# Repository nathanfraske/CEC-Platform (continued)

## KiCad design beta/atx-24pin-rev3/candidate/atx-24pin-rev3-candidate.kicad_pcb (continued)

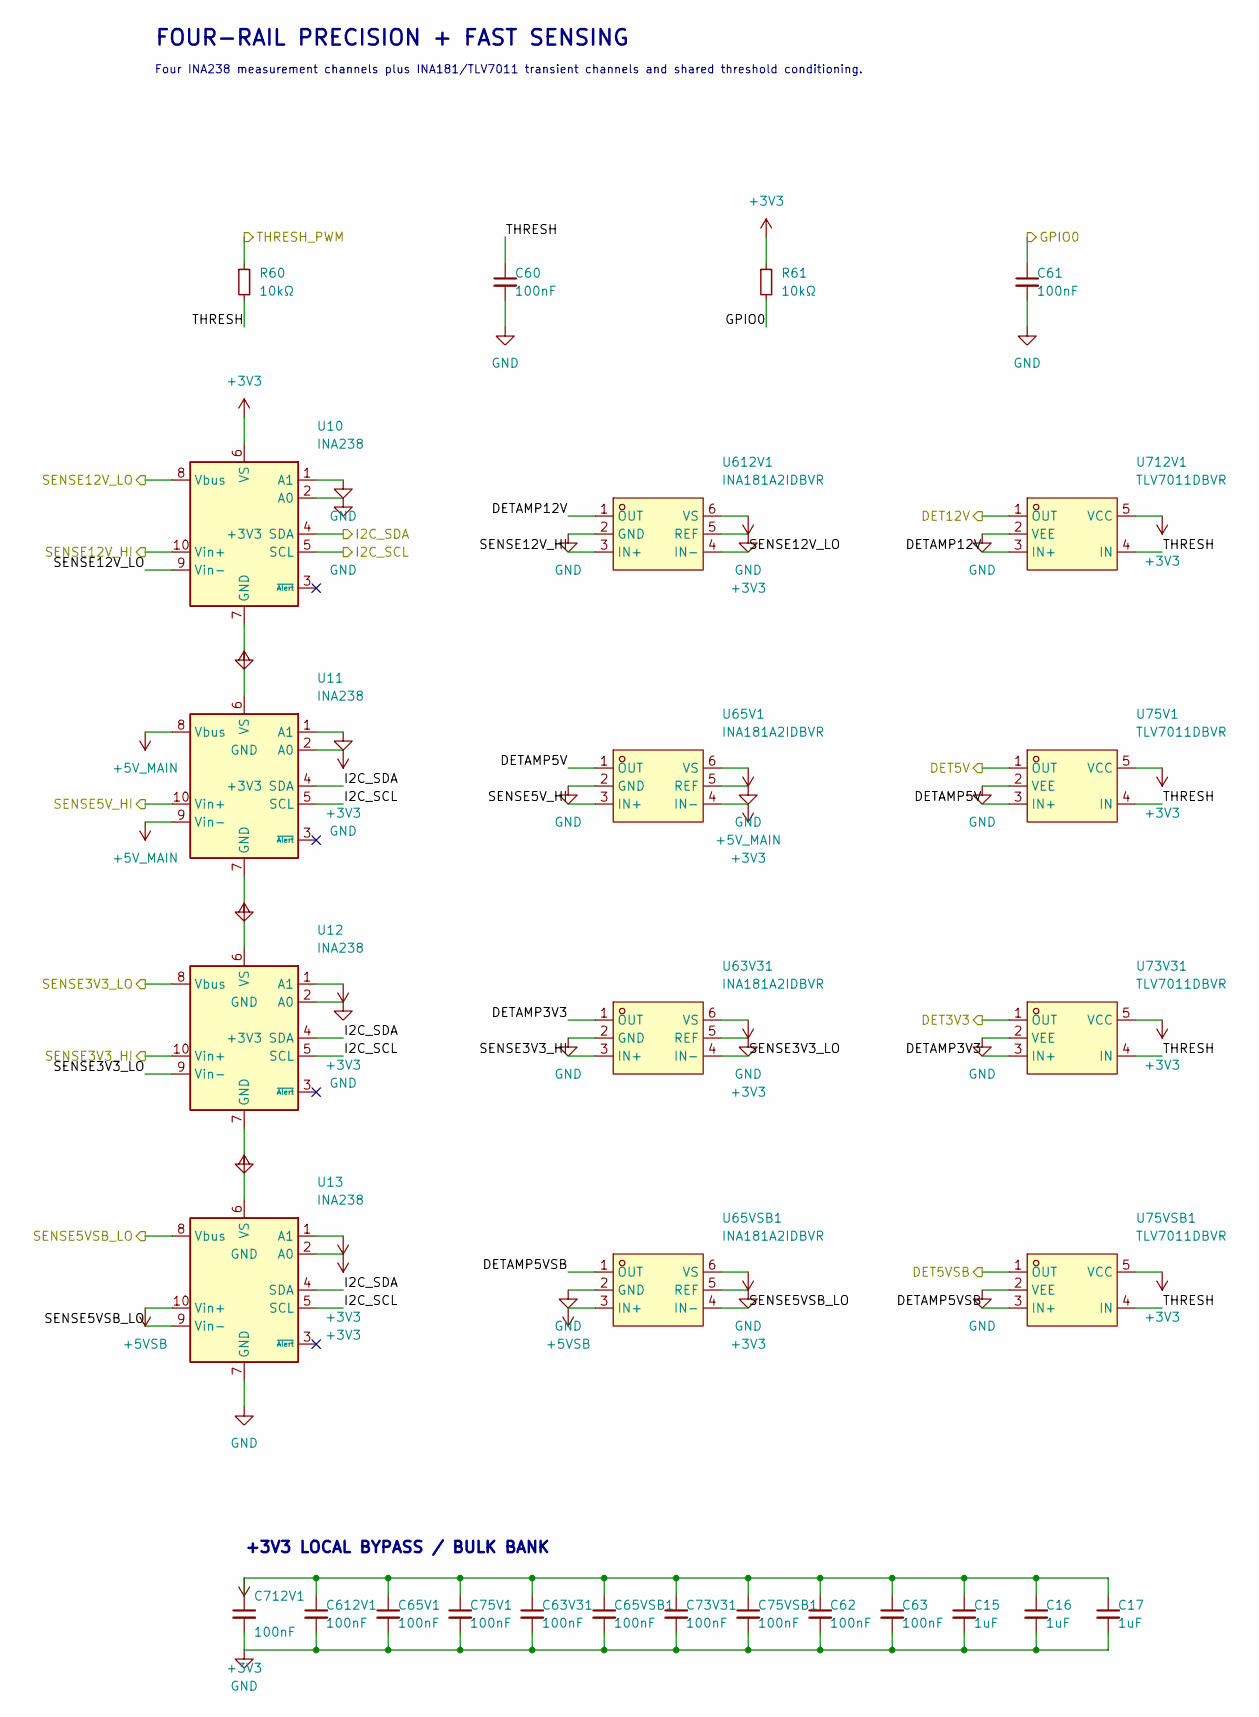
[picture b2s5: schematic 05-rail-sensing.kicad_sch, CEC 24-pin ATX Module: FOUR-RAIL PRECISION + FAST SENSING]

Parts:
C15, C16, C17: 1uF; C_0603_1608Metric; MPN CL10B105KA8NNNC; LCSC C29936
C60, C61, C62, C63, C63V31, C65V1, C65VSB1, C73V31, C75V1, C75VSB1, C612V1, C712V1: 100nF; C_0402_1005Metric; MPN CL05B104KO5NNNC; LCSC C1525
R60, R61: 10kΩ; R_0402_1005Metric; MPN 0402WGF1002TCE; LCSC C25744
U10, U11, U12, U13: INA238; VSSOP-10_3x3mm_P0.5mm; MPN INA238AIDGSR; LCSC C2868250
U63V31, U65V1, U65VSB1, U612V1: INA181A2IDBVR; SOT-23-6; MPN INA181A2IDBVR; LCSC C2058784
U73V31, U75V1, U75VSB1, U712V1: TLV7011DBVR; SOT-23-5; MPN TLV7011DBVR; LCSC C702117

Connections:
+3V3: C15.1, C16.1, C17.1, C62.1, C63.1, C63V31.1, C65V1.1, C65VSB1.1, C73V31.1, C75V1.1, C75VSB1.1, C612V1.1, C712V1.1, R61.1, U10.6 (VS), U11.2 (A0), U11.6 (VS), U12.1 (A1), U12.6 (VS), U13.1 (A1), U13.2 (A0), U13.6 (VS), U63V31.6 (VS), U65V1.6 (VS), U65VSB1.6 (VS), U73V31.5 (VCC), U75V1.5 (VCC), U75VSB1.5 (VCC), U612V1.6 (VS), U712V1.5 (VCC); also elsewhere on the board
+5VSB: U13.10 (Vin+), U65VSB1.3 (IN+); also elsewhere on the board
+5V_MAIN: U11.8 (Vbus), U11.9 (Vin-), U65V1.4 (IN-); also elsewhere on the board
/DET3V3: U73V31.1 (OUT); also elsewhere on the board
/DET5V: U75V1.1 (OUT); also elsewhere on the board
/DET5VSB: U75VSB1.1 (OUT); also elsewhere on the board
/DET12V: U712V1.1 (OUT); also elsewhere on the board
/FOUR-RAIL PRECISION + FAST SENSING/DETAMP3V3: U63V31.1 (OUT), U73V31.3 (IN+)
/FOUR-RAIL PRECISION + FAST SENSING/DETAMP5V: U65V1.1 (OUT), U75V1.3 (IN+)
/FOUR-RAIL PRECISION + FAST SENSING/DETAMP5VSB: U65VSB1.1 (OUT), U75VSB1.3 (IN+)
/FOUR-RAIL PRECISION + FAST SENSING/DETAMP12V: U612V1.1 (OUT), U712V1.3 (IN+)
/FOUR-RAIL PRECISION + FAST SENSING/THRESH: C60.1, R60.2, U73V31.4 (IN), U75V1.4 (IN), U75VSB1.4 (IN), U712V1.4 (IN)
/GPIO0: C61.1, R61.2; also elsewhere on the board
/I2C_SCL: U10.5 (SCL), U11.5 (SCL), U12.5 (SCL), U13.5 (SCL); also elsewhere on the board
/I2C_SDA: U10.4 (SDA), U11.4 (SDA), U12.4 (SDA), U13.4 (SDA); also elsewhere on the board
/SENSE3V3_HI: U12.10 (Vin+), U63V31.3 (IN+); also elsewhere on the board
/SENSE3V3_LO: U12.8 (Vbus), U12.9 (Vin-), U63V31.4 (IN-); also elsewhere on the board
/SENSE5VSB_LO: U13.8 (Vbus), U13.9 (Vin-), U65VSB1.4 (IN-); also elsewhere on the board
/SENSE5V_HI: U11.10 (Vin+), U65V1.3 (IN+); also elsewhere on the board
/SENSE12V_HI: U10.10 (Vin+), U612V1.3 (IN+); also elsewhere on the board
/SENSE12V_LO: U10.8 (Vbus), U10.9 (Vin-), U612V1.4 (IN-); also elsewhere on the board
/THRESH_PWM: R60.1; also elsewhere on the board
GND: C15.2, C16.2, C17.2, C60.2, C61.2, C62.2, C63.2, C63V31.2, C65V1.2, C65VSB1.2, C73V31.2, C75V1.2, C75VSB1.2, C612V1.2, C712V1.2, U10.1 (A1), U10.2 (A0), U10.7 (GND), U11.1 (A1), U11.7 (GND), U12.2 (A0), U12.7 (GND), U13.7 (GND), U63V31.2 (GND), U63V31.5 (REF), U65V1.2 (GND), U65V1.5 (REF), U65VSB1.2 (GND), U65VSB1.5 (REF), U73V31.2 (VEE), U75V1.2 (VEE), U75VSB1.2 (VEE), U612V1.2 (GND), U612V1.5 (REF), U712V1.2 (VEE); also elsewhere on the board

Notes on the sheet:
FOUR-RAIL PRECISION + FAST SENSING
Four INA238 measurement channels plus INA181/TLV7011 transient channels and shared threshold conditioning.
+3V3 LOCAL BYPASS / BULK BANK

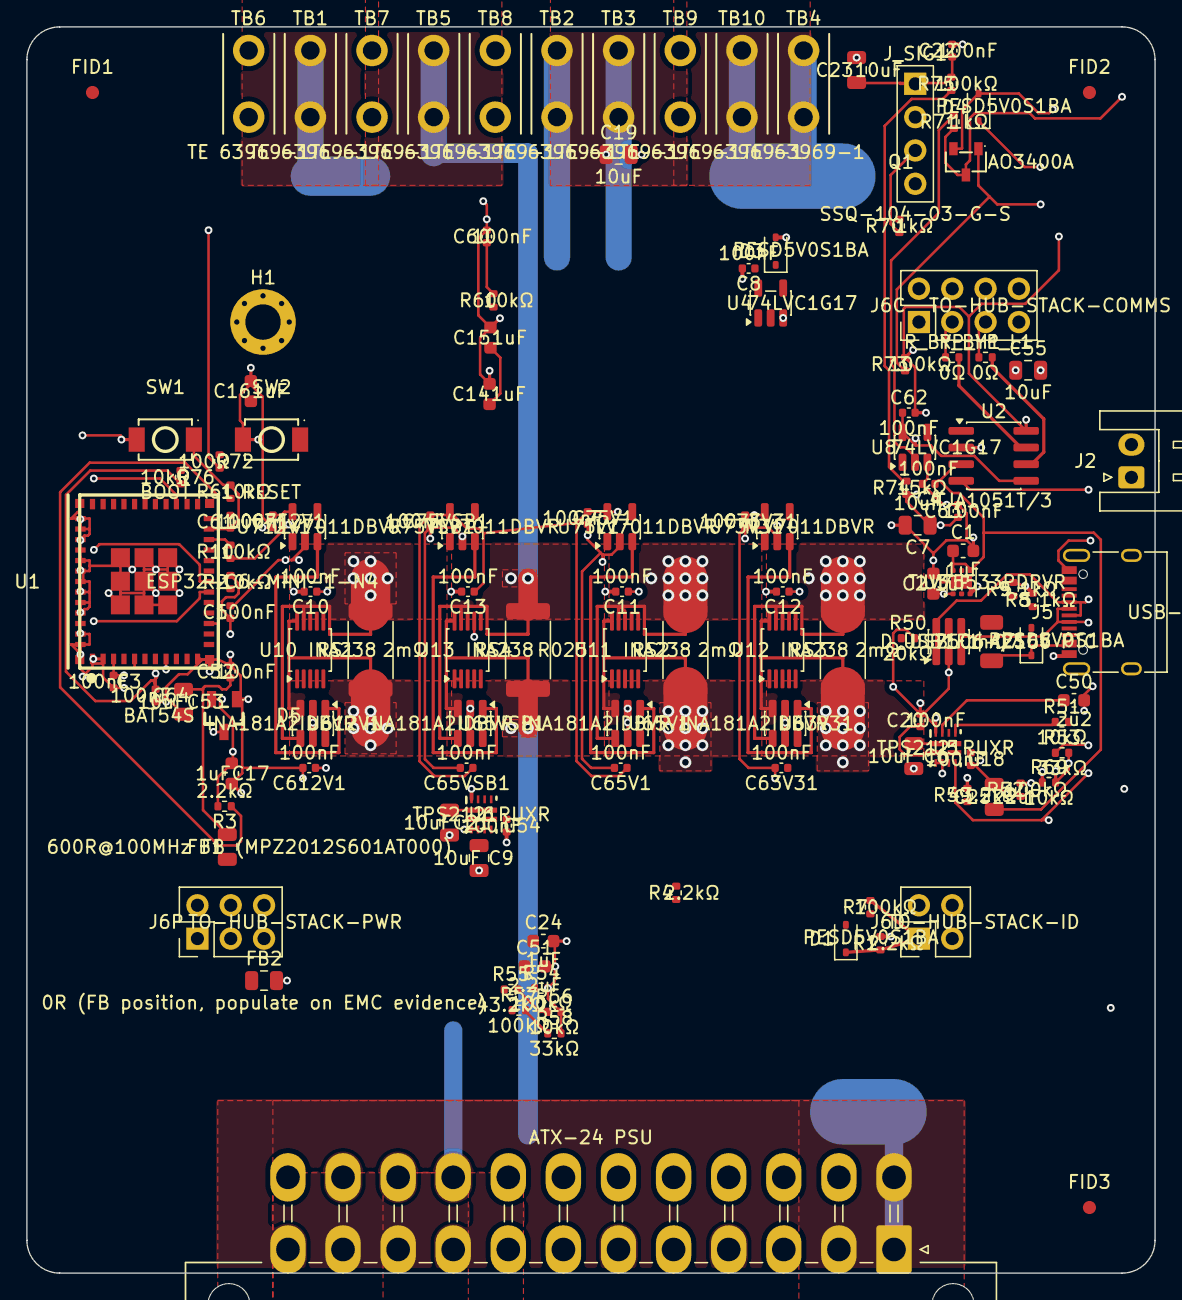
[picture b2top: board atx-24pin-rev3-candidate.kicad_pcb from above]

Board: 6 copper layers, 86.0 x 95.0 mm, 130 parts (0 on the bottom side), 63 nets.

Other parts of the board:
FID1, FID2, FID3: Fiducial_1mm_Mask2mm
H1: MountingHole_2.7mm_M2.5_Pad_Via

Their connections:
GND: H1.1; also elsewhere on the board

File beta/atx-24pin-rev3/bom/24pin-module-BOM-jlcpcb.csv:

"Comment","Designator","Footprint","LCSC Part #"
"1uF","C1,C2,C14,C15,C16,C17,C24","cec-Capacitor_SMD:C_0603_1608Metric","C29936"
"22uF","C25","cec-Capacitor_SMD:C_0805_2012Metric","C45783"
"100nF","C3,C4,C5,C8,C10,C11,C12,C13,C18,C20,C22,C52,C54,C60,C61,C62,C63,C63V31,C64,C65V1,C65VSB1,C73V31,C75V1,C75VSB1,C612V1,C712V1","cec-Capacitor_SMD:C_0402_1005Metric","C1525"
"2u2","C50","cec-Capacitor_SMD:C_0603_1608Metric","C23630"
"2.2uF","C51","cec-Capacitor_SMD:C_0603_1608Metric","C23630"
"10uF","C6,C7,C9,C19,C21,C23,C53,C55","cec-Capacitor_SMD:C_0805_2012Metric","C15850"
"PESD5V0S1BA","D1,D3,D4,D7","cec-Diode_SMD:D_SOD-323","C5261083"
"BAT54S","D5","cec-Package_TO_SOT_SMD:SOT-23-3_L2.9-W1.3-P1.90-LS2.4-TL","C545549"
"USBLC6-2SC6","D_USB1","cec-Package_TO_SOT_SMD:SOT-23-6","C7519"
"750mA/16V PTC","F1","cec-Resistor_SMD:R_1206_3216Metric","C371166"
"600R@100MHz FB (MPZ2012S601AT000)","FB1","cec-Capacitor_SMD:C_0805_2012Metric","C21519"
"0R (FB position, populate on EMC evidence)","FB2","cec-Capacitor_SMD:C_0805_2012Metric","C17477"
"TO-HUB-PWR","J2","cec-Connector_JST:JST_XH_S2B-XH-A_1x02_P2.50mm_Horizontal","C157931"
"ATX-24 PSU","J3","cec-Connector_Molex:Molex_Mini-Fit_Jr_5569-24A1_2x12_P4.20mm_Horizontal",""
"USB-C 2.0","J5","cec-Connector_USB:USB_C_Receptacle_XKB_U262-16XN-4BVC11","C319148"
"TO-HUB-STACK-COMMS","J6C?","cec-Connector_PinHeader_2.54mm:PinHeader_2x04_P2.54mm_Vertical",""
"TO-HUB-STACK-ID","J6D?","cec-Connector_PinHeader_2.54mm:PinHeader_2x02_P2.54mm_Vertical",""
"TO-HUB-STACK-PWR","J6P?","cec-Connector_PinHeader_2.54mm:PinHeader_2x03_P2.54mm_Vertical",""
"SSQ-104-03-G-S","J_SIG1","cec-Connector_PinSocket_2.54mm:PinSocket_1x04_P2.54mm_Vertical",""
"AO3400A","Q1","cec-Package_TO_SOT_SMD:SOT-23-3_L2.9-W1.3-P1.90-LS2.4-BR","C20917"
"2.2kΩ","R1,R3,R4","cec-Resistor_SMD:R_0402_1005Metric","C25879"
"10kΩ","R2,R10,R51,R56,R60,R61,R69,R76","cec-Resistor_SMD:R_0402_1005Metric","C25744"
"20kΩ","R50","cec-Resistor_SMD:R_0402_1005Metric","C25765"
"33kΩ","R53,R58","cec-Resistor_SMD:R_0402_1005Metric","C25779"
"43.2kΩ","R55,R59","cec-Resistor_SMD:R_0402_1005Metric","C25894"
"100kΩ","R7,R52,R54,R57,R73,R75","cec-Resistor_SMD:R_0402_1005Metric","C25741"
"1kΩ","R70,R71","cec-Resistor_SMD:R_0402_1005Metric","C11702"
"100Ω","R72","cec-Resistor_SMD:R_0402_1005Metric","C106233"
"15kΩ","R74","cec-Resistor_SMD:R_0402_1005Metric","C25756"
"5.1kΩ","R8,R9","cec-Resistor_SMD:R_0402_1005Metric","C25905"
"2mΩ","RS1,RS2,RS3","cec-Resistor_SMD:R_2512_6332Metric","C1729157"
"R025","RS4","cec-Resistor_SMD:R_2512_6332Metric","C494568"
"0Ω","R_BYP_H1,R_BYP_L1","cec-Resistor_SMD:R_0402_1005Metric","C17168"
"BOOT","SW1","cec-Button_Switch_SMD:TS-1088-AR02016","C720477"
"RESET","SW2","cec-Button_Switch_SMD:TS-1088-AR02016","C720477"
"TE 63969-1","TB1,TB2,TB3,TB4,TB5,TB6,TB7,TB8,TB9,TB10","cec-Connector_Blade:TE_63969_FASTON_Receptacle_250_Vertical_THT","C2961150"
"ESP32-C6-MINI-1-N4","U1","cec-RF_Module:ESP32-C6-MINI-1","C5736265"
"INA238","U10,U11,U12,U13","cec-Package_SO:VSSOP-10_3x3mm_P0.5mm","C2868250"
"TJA1051T/3","U2","cec-Package_SO:SOIC-8_3.9x4.9mm_P1.27mm","C38695"
"TLV75533PDRVR","U3","cec-Package_SON:WSON-6-1EP_2x2mm_P0.65mm_EP1x1.6mm","C2861750"
"74LVC1G17","U4,U8","cec-Package_TO_SOT_SMD:SOT-23-5","C7836"
"TPS2121RUXR","U5,U6","cec-Package_DFN_QFN:RUX0012A","C485916"
"INA181A2IDBVR","U63V31,U65V1,U65VSB1,U612V1","cec-Package_TO_SOT_SMD:SOT-23-6","C2058784"
"TLV7011DBVR","U73V31,U75V1,U75VSB1,U712V1","cec-Package_TO_SOT_SMD:SOT-23-5","C702117"

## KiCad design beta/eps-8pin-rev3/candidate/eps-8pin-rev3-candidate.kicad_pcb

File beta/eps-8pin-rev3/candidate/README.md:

# `candidate/`: the current best routed board for this module

ONE board file, kept current by the wave (owner directive 2026-07-25: "the current
best should be placed into a candidate folder per board and kept current with only
one board ideally so we have a reference").

`<board>-candidate.kicad_pcb` (+ its `.kicad_pro` / `.kicad_dru` sidecars) is a COPY
of the best board the wave has ever published for this module, with `candidate.json`
recording where it came from and how it graded. Open it to see the real current
state of the layout without digging through `build/fresh-wave-*/`.

RULES the wave enforces on every publish:
  * SCHEMATIC FRESHNESS outranks score: a winner matching more of the CURRENT
    component signatures replaces the reference even on a worse score, and a
    staler board never replaces a fresher one. The signature covers value,
    footprint, and numbered-pad nets. `schematic_match` and `schematic_exact` in
    `candidate.json` record the result. A board that grades well but predates a
    schematic or footprint change is the worse reference;
  * otherwise it replaces this file only when the new winner BEATS the recorded
    `sort_key` (lower is better -- the same ranking the wave itself uses);
  * a routed winner always beats a placement-only one, and a placement-only winner
    NEVER overwrites a routed reference;
  * exactly one `.kicad_pcb` lives here -- stale board files are pruned.

`candidate.json` is also refreshable without publishing a board. Consumers that
use a candidate as a placement oracle or materialization template MUST require
`schematic_exact: true` after a current refresh. A stale candidate remains useful
for historical outline, connector, mount, and copper review, but it is not a
component-inventory or pin/net authority.

This is a REFERENCE, not the board of record: it is machine-written, so never hand-edit
it (edits are silently overwritten by the next better wave). The authoritative
schematic + the module's own project files stay in the parent directory.

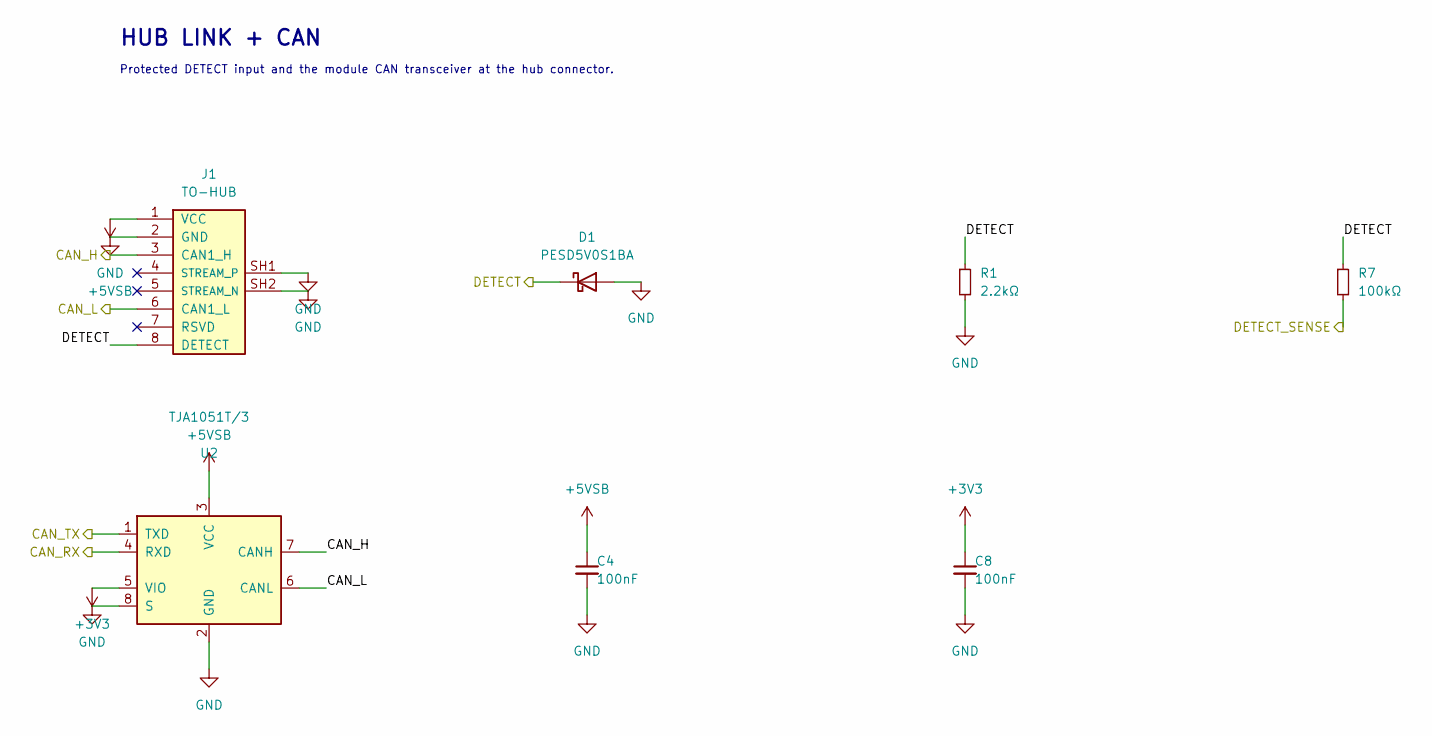
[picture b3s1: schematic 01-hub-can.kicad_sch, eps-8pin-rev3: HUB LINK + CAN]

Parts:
C4, C8: 100nF; C_0402_1005Metric; MPN CL05B104KO5NNNC; LCSC C1525
D1: PESD5V0S1BA; D_SOD-323; MPN PESD5V0S1BA; LCSC C5261083
J1: TO-HUB; RJ45_FTP_Shielded_Horizontal; MPN KH-RJ45-58-8P8C; LCSC C2683360
R1: 2.2kΩ; R_0402_1005Metric; MPN 0402WGF2201TCE; LCSC C25879
R7: 100kΩ; R_0402_1005Metric; MPN 0402WGF1003TCE; LCSC C25741
U2: TJA1051T/3; SOIC-8_3.9x4.9mm_P1.27mm; MPN TJA1051T/3/1J; LCSC C38695

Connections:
+3V3: C8.1, U2.5 (VIO); also elsewhere on the board
+5VSB: C4.1, J1.1 (VCC), U2.3 (VCC); also elsewhere on the board
/CAN_H: J1.3 (CAN1_H), U2.7 (CANH)
/CAN_L: J1.6 (CAN1_L), U2.6 (CANL)
/CAN_RX: U2.4 (RXD); also elsewhere on the board
/CAN_TX: U2.1 (TXD); also elsewhere on the board
/DETECT: D1.1 (K), J1.8 (DETECT), R1.1, R7.1
/DETECT_SENSE: R7.2; also elsewhere on the board
GND: C4.2, C8.2, D1.2 (A), J1.2 (GND), J1.SH1, J1.SH2, R1.2, U2.2 (GND), U2.8 (S); also elsewhere on the board

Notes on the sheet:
HUB LINK + CAN
Protected DETECT input and the module CAN transceiver at the hub connector.

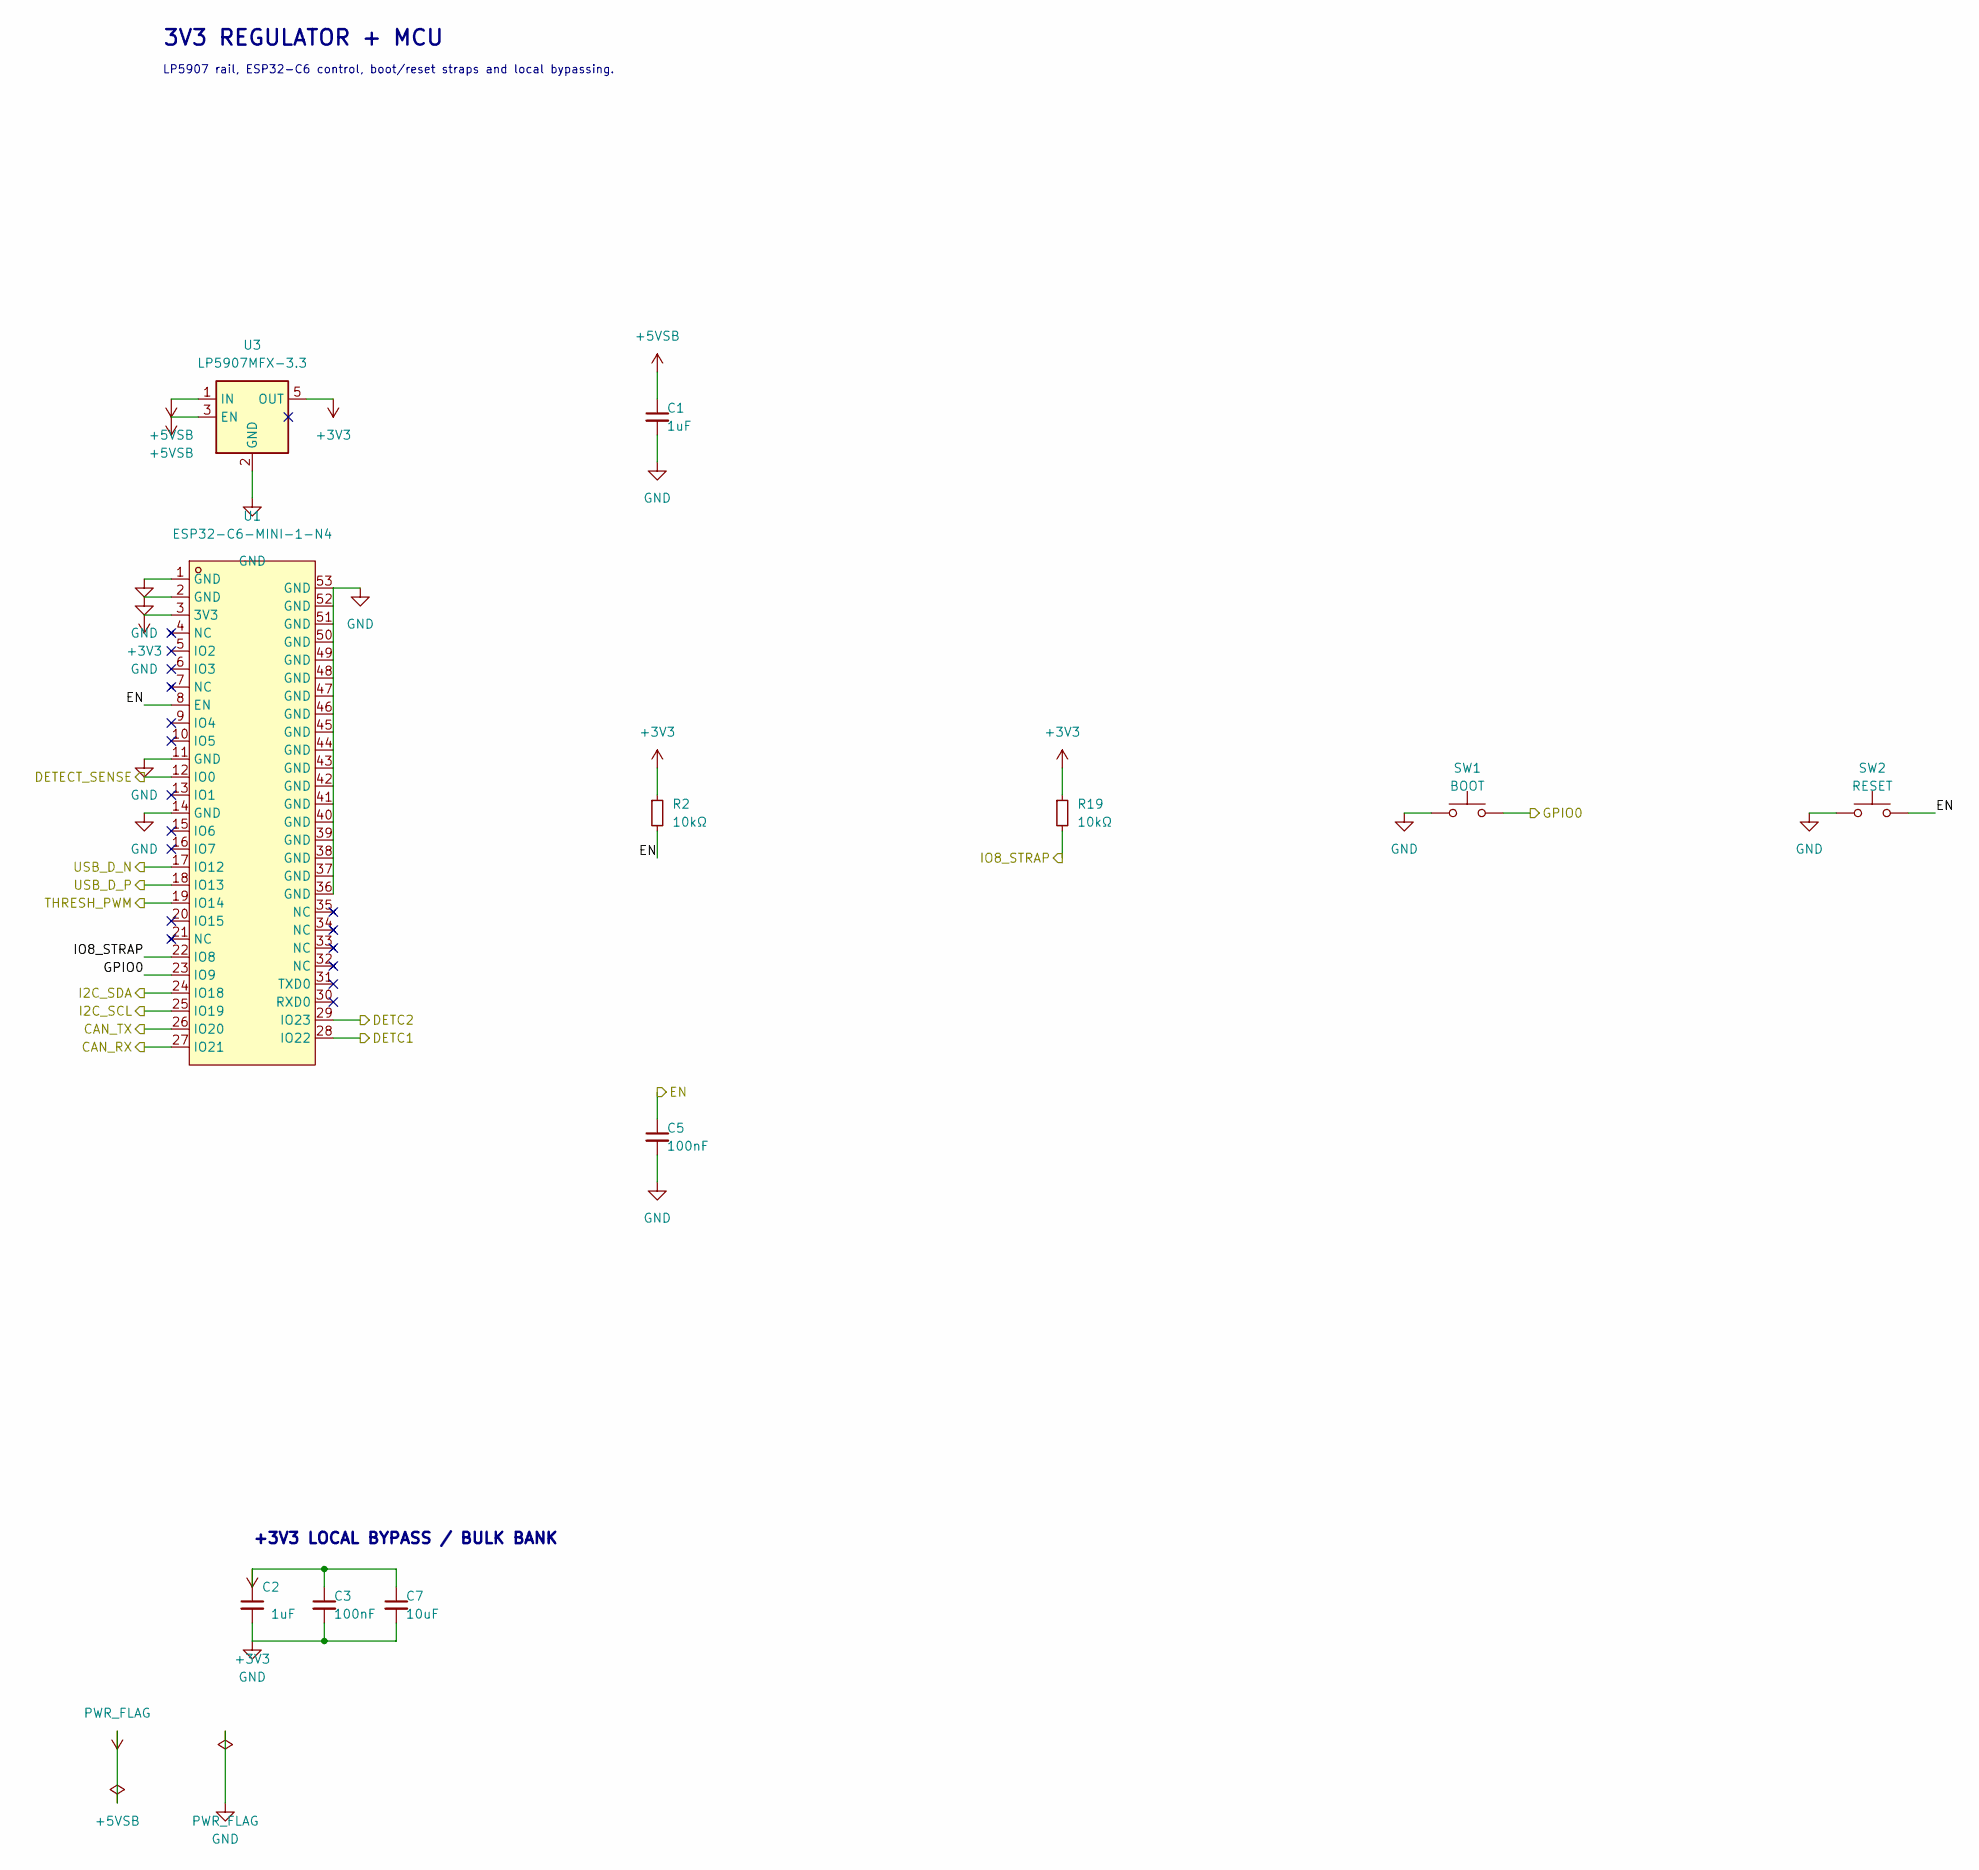
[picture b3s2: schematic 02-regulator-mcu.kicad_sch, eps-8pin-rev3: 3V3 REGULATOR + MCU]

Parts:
C1, C2: 1uF; C_0603_1608Metric; MPN CL10A105KB8NNNC; LCSC C15849
C3, C5: 100nF; C_0402_1005Metric; MPN CL05B104KO5NNNC; LCSC C1525
C7: 10uF; C_0805_2012Metric; MPN CL21A106KAYNNNE; LCSC C15850
R2, R19: 10kΩ; R_0402_1005Metric; MPN 0402WGF1002TCE; LCSC C25744
SW1: BOOT; TS-1088-AR02016; MPN TS-1088-AR02016; LCSC C720477
SW2: RESET; TS-1088-AR02016; MPN TS-1088-AR02016; LCSC C720477
U1: ESP32-C6-MINI-1-N4; ESP32-C6-MINI-1; MPN ESP32-C6-MINI-1-N4; LCSC C5736265
U3: LP5907MFX-3.3; SOT-23-5; MPN LP5907MFX-3.3/NOPB; LCSC C80670

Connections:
+3V3: C2.1, C3.1, C7.1, R2.1, R19.1, U1.3 (3V3), U3.5 (OUT); also elsewhere on the board
+5VSB: C1.1, U3.1 (IN), U3.3 (EN); also elsewhere on the board
/CAN_RX: U1.27 (IO21); also elsewhere on the board
/CAN_TX: U1.26 (IO20); also elsewhere on the board
/DETC1: U1.28 (IO22); also elsewhere on the board
/DETC2: U1.29 (IO23); also elsewhere on the board
/DETECT_SENSE: U1.12 (IO0); also elsewhere on the board
/EN: C5.1, R2.2, SW2.2, U1.8 (EN)
/GPIO0: SW1.2, U1.23 (IO9)
/I2C_SCL: U1.25 (IO19); also elsewhere on the board
/I2C_SDA: U1.24 (IO18); also elsewhere on the board
/IO8_STRAP: R19.2, U1.22 (IO8)
/THRESH_PWM: U1.19 (IO14); also elsewhere on the board
/USB_D_N: U1.17 (IO12); also elsewhere on the board
/USB_D_P: U1.18 (IO13); also elsewhere on the board
GND: C1.2, C2.2, C3.2, C5.2, C7.2, SW1.1, SW2.1, U1.1 (GND), U1.2 (GND), U1.11 (GND), U1.14 (GND), U1.36 (GND), U1.37 (GND), U1.38 (GND), U1.39 (GND), U1.40 (GND), U1.41 (GND), U1.42 (GND), U1.43 (GND), U1.44 (GND), U1.45 (GND), U1.46 (GND), U1.47 (GND), U1.48 (GND), U1.49 (GND), U1.50 (GND), U1.51 (GND), U1.52 (GND), U1.53 (GND), U3.2 (GND); also elsewhere on the board

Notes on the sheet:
3V3 REGULATOR + MCU
LP5907 rail, ESP32-C6 control, boot/reset straps and local bypassing.
+3V3 LOCAL BYPASS / BULK BANK

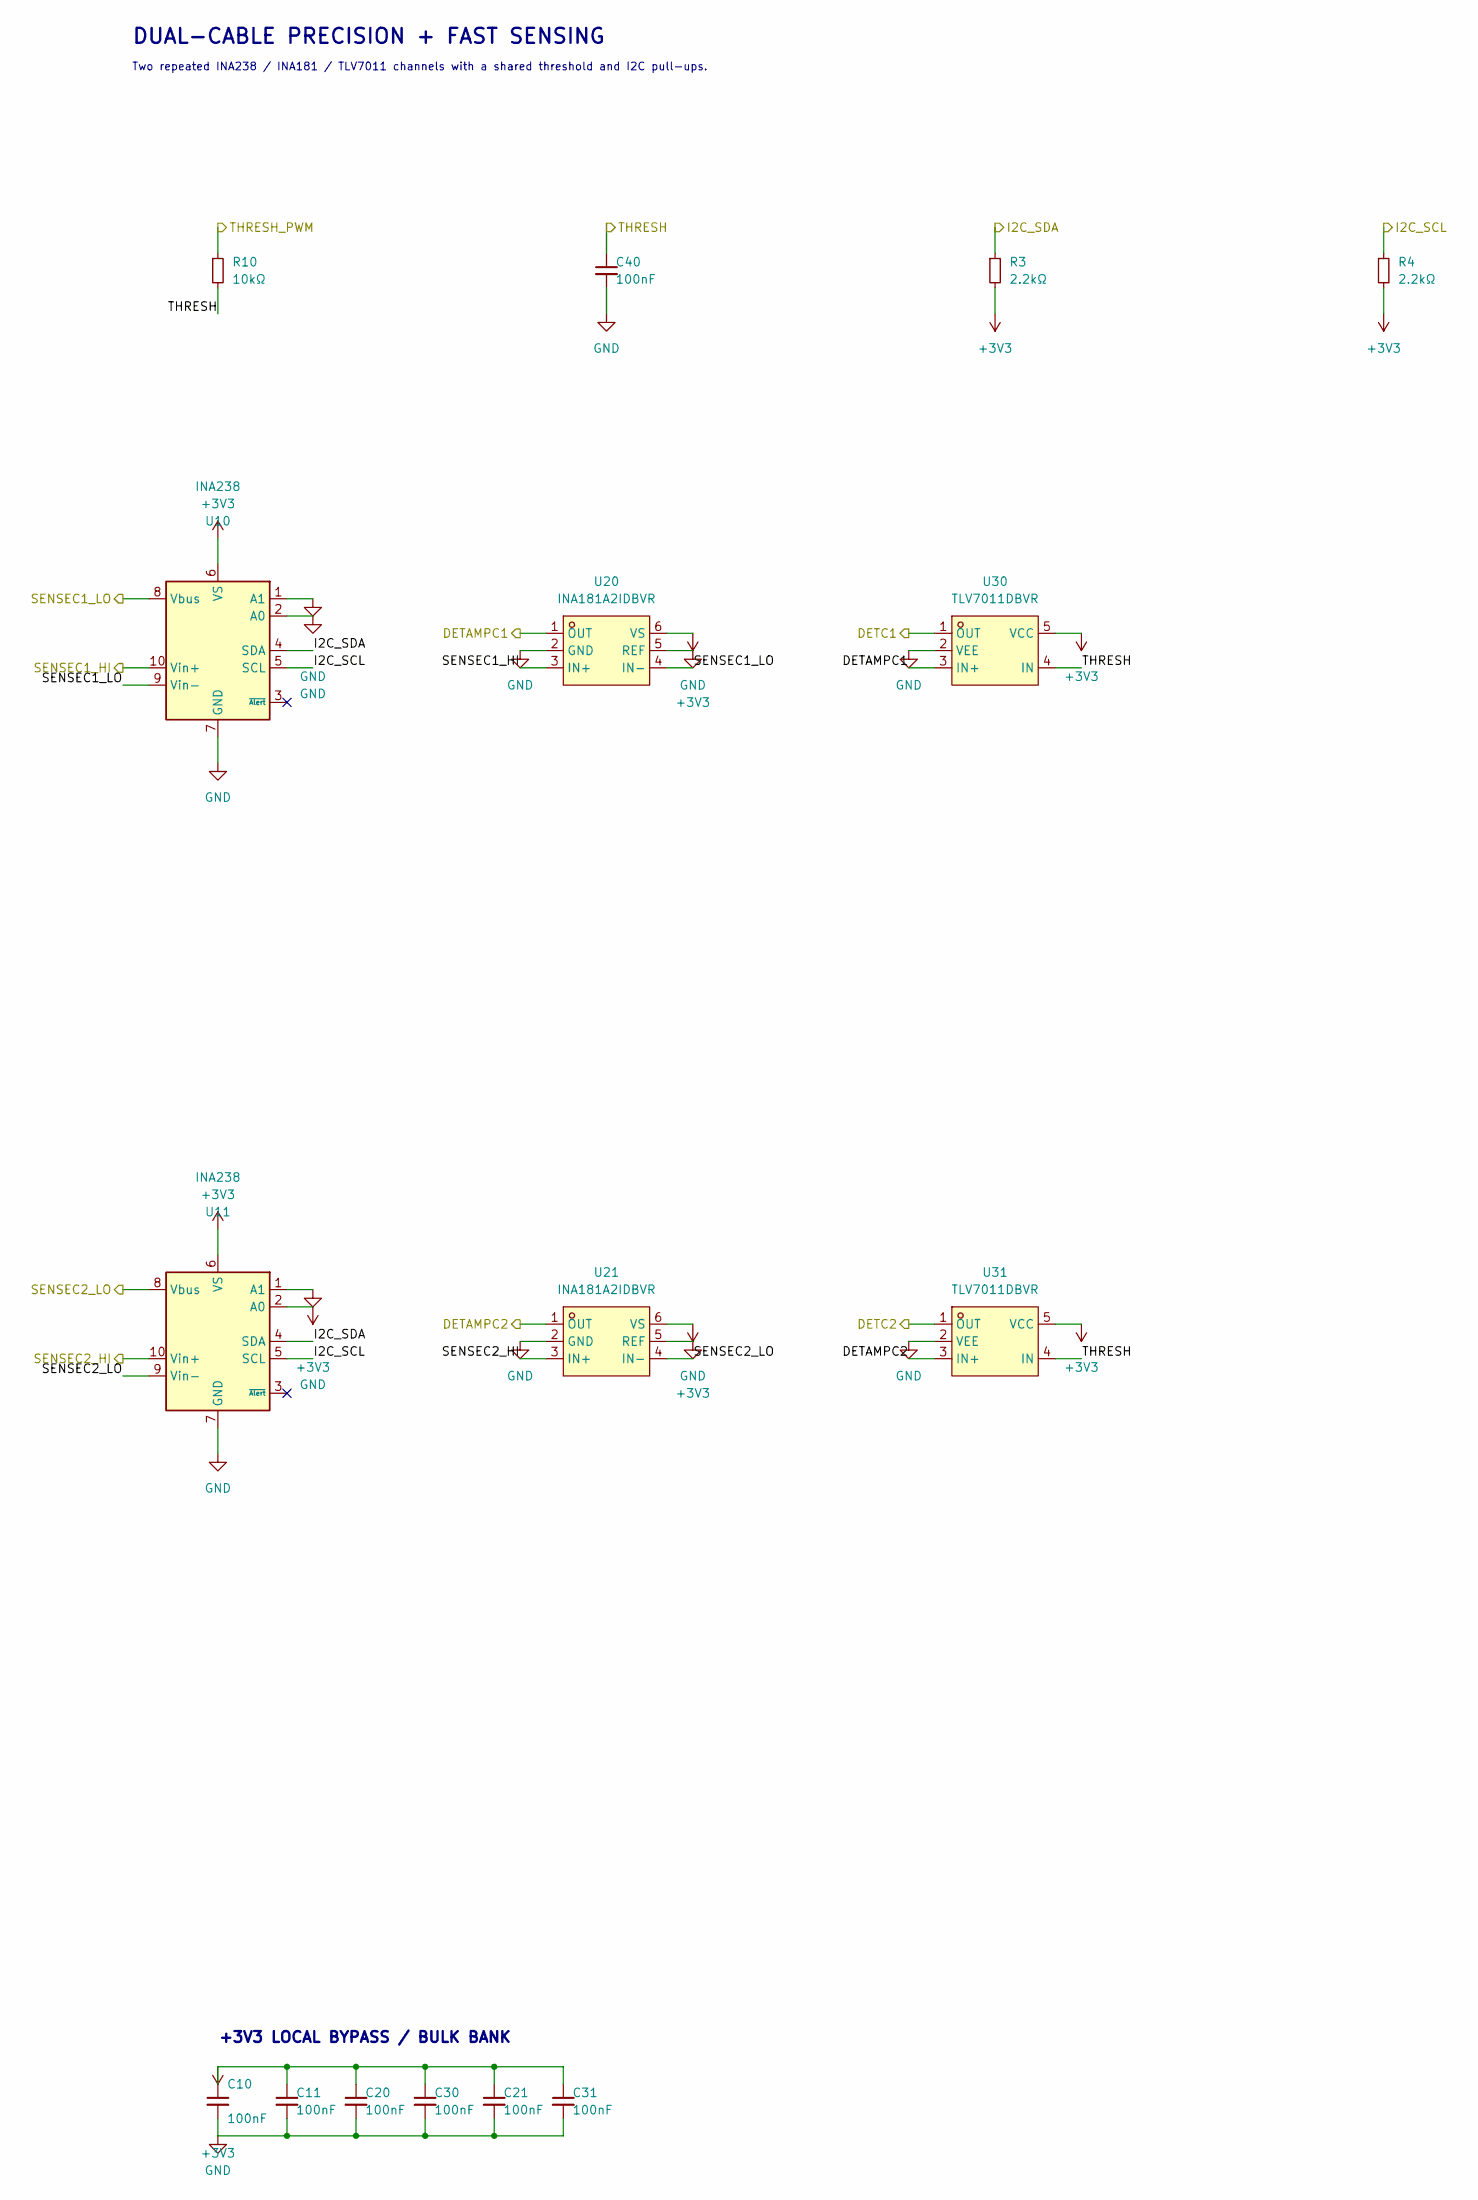
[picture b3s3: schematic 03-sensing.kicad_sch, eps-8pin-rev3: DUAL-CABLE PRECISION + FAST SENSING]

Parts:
C10, C11, C20, C21, C30, C31, C40: 100nF; C_0402_1005Metric; MPN CL05B104KO5NNNC; LCSC C1525
R3, R4: 2.2kΩ; R_0402_1005Metric; MPN 0402WGF2201TCE; LCSC C25879
R10: 10kΩ; R_0402_1005Metric; MPN 0402WGF1002TCE; LCSC C25744
U10, U11: INA238; VSSOP-10_3x3mm_P0.5mm; MPN INA238AIDGSR; LCSC C2868250
U20, U21: INA181A2IDBVR; SOT-23-6; MPN INA181A2IDBVR; LCSC C2058784
U30, U31: TLV7011DBVR; SOT-23-5; MPN TLV7011DBVR; LCSC C702117

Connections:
+3V3: C10.1, C11.1, C20.1, C21.1, C30.1, C31.1, R3.2, R4.2, U10.6 (VS), U11.2 (A0), U11.6 (VS), U20.6 (VS), U21.6 (VS), U30.5 (VCC), U31.5 (VCC); also elsewhere on the board
/DETAMPC1: U20.1 (OUT), U30.3 (IN+)
/DETAMPC2: U21.1 (OUT), U31.3 (IN+)
/DETC1: U30.1 (OUT); also elsewhere on the board
/DETC2: U31.1 (OUT); also elsewhere on the board
/I2C_SCL: R4.1, U10.5 (SCL), U11.5 (SCL); also elsewhere on the board
/I2C_SDA: R3.1, U10.4 (SDA), U11.4 (SDA); also elsewhere on the board
/SENSEC1_HI: U10.10 (Vin+), U20.3 (IN+); also elsewhere on the board
/SENSEC1_LO: U10.8 (Vbus), U10.9 (Vin-), U20.4 (IN-); also elsewhere on the board
/SENSEC2_HI: U11.10 (Vin+), U21.3 (IN+); also elsewhere on the board
/SENSEC2_LO: U11.8 (Vbus), U11.9 (Vin-), U21.4 (IN-); also elsewhere on the board
/THRESH: C40.1, R10.2, U30.4 (IN), U31.4 (IN)
/THRESH_PWM: R10.1; also elsewhere on the board
GND: C10.2, C11.2, C20.2, C21.2, C30.2, C31.2, C40.2, U10.1 (A1), U10.2 (A0), U10.7 (GND), U11.1 (A1), U11.7 (GND), U20.2 (GND), U20.5 (REF), U21.2 (GND), U21.5 (REF), U30.2 (VEE), U31.2 (VEE); also elsewhere on the board

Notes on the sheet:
DUAL-CABLE PRECISION + FAST SENSING
Two repeated INA238 / INA181 / TLV7011 channels with a shared threshold and I2C pull-ups.
+3V3 LOCAL BYPASS / BULK BANK

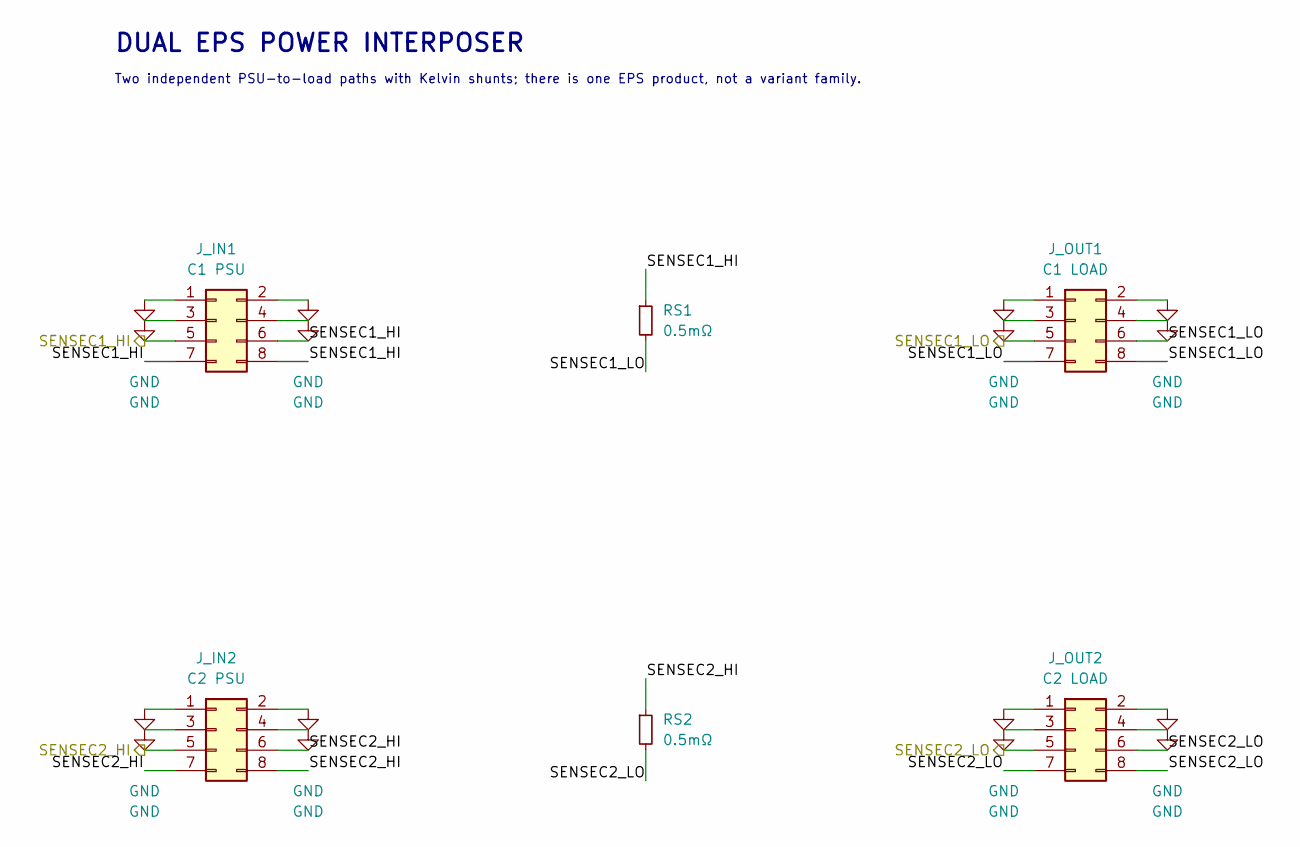
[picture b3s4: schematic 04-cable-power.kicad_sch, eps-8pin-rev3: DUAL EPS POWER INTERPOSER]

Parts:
J_IN1: C1 PSU; Molex_Mini-Fit_Jr_87427-0802_2x04_P4.20mm_RA; MPN 87427-0802
J_IN2: C2 PSU; Molex_Mini-Fit_Jr_87427-0802_2x04_P4.20mm_RA; MPN 87427-0802
J_OUT1: C1 LOAD; Molex_Mini-Fit_Jr_87427-0802_2x04_P4.20mm_RA; MPN 87427-0802
J_OUT2: C2 LOAD; Molex_Mini-Fit_Jr_87427-0802_2x04_P4.20mm_RA; MPN 87427-0802
RS1, RS2: 0.5mΩ; R_2512_6332Metric; MPN CSS2H-2512R-L500F

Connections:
/SENSEC1_HI: J_IN1.5, J_IN1.6, J_IN1.7, J_IN1.8, RS1.1; also elsewhere on the board
/SENSEC1_LO: J_OUT1.5, J_OUT1.6, J_OUT1.7, J_OUT1.8, RS1.2; also elsewhere on the board
/SENSEC2_HI: J_IN2.5, J_IN2.6, J_IN2.7, J_IN2.8, RS2.1; also elsewhere on the board
/SENSEC2_LO: J_OUT2.5, J_OUT2.6, J_OUT2.7, J_OUT2.8, RS2.2; also elsewhere on the board
GND: J_IN1.1, J_IN1.2, J_IN1.3, J_IN1.4, J_IN2.1, J_IN2.2, J_IN2.3, J_IN2.4, J_OUT1.1, J_OUT1.2, J_OUT1.3, J_OUT1.4, J_OUT2.1, J_OUT2.2, J_OUT2.3, J_OUT2.4; also elsewhere on the board

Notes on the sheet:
DUAL EPS POWER INTERPOSER
Two independent PSU-to-load paths with Kelvin shunts; there is one EPS product, not a variant family.

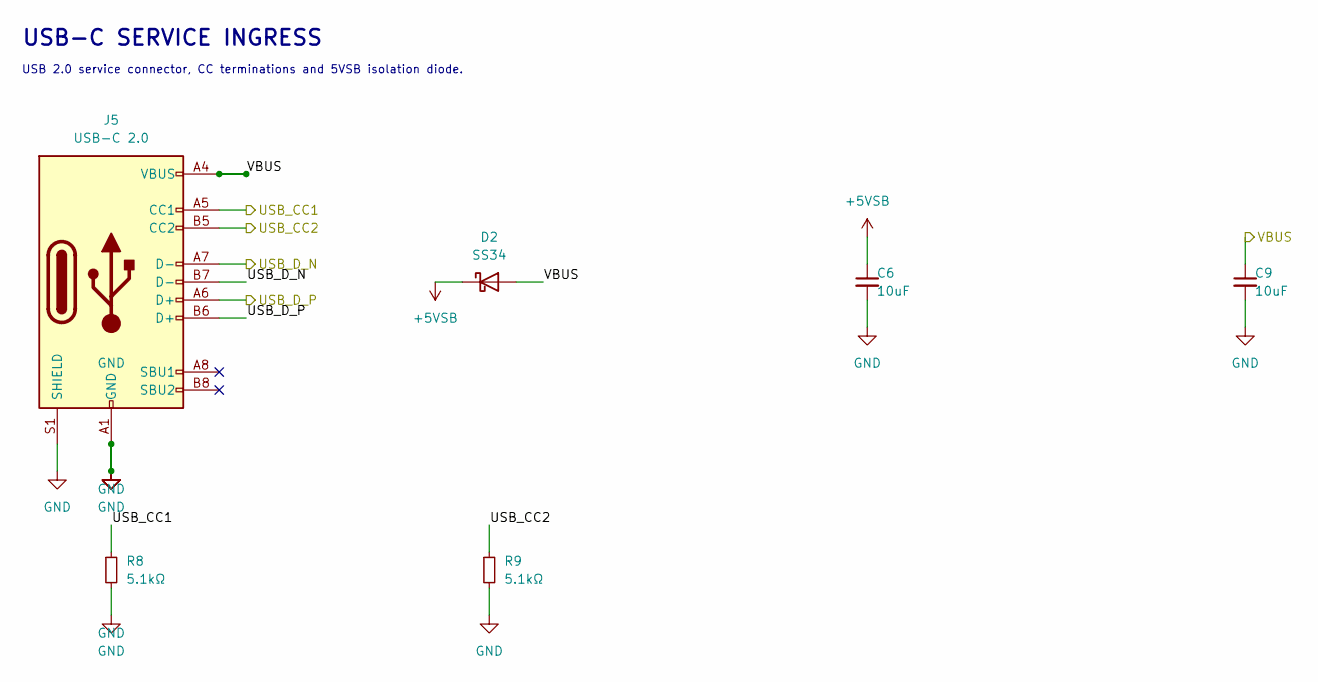
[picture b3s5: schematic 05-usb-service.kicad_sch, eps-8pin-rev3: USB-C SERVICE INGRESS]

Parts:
C6, C9: 10uF; C_0805_2012Metric; MPN CL21A106KAYNNNE; LCSC C15850
D2: SS34; D_SMA; MPN SS34; LCSC C8678
J5: USB-C 2.0; USB_C_Receptacle_XKB_U262-16XN-4BVC11; MPN U262-161N-4BVC11; LCSC C319148
R8, R9: 5.1kΩ; R_0402_1005Metric; MPN 0402WGF5101TCE; LCSC C25905

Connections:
+5VSB: C6.1, D2.1 (K); also elsewhere on the board
/USB_CC1: J5.A5 (CC1), R8.1
/USB_CC2: J5.B5 (CC2), R9.1
/USB_D_N: J5.A7 (D-), J5.B7 (D-); also elsewhere on the board
/USB_D_P: J5.A6 (D+), J5.B6 (D+); also elsewhere on the board
/VBUS: C9.1, D2.2 (A), J5.A4 (VBUS), J5.A9 (VBUS), J5.B4 (VBUS), J5.B9 (VBUS)
GND: C6.2, C9.2, J5.A1 (GND), J5.A12 (GND), J5.B1 (GND), J5.B12 (GND), J5.S1 (SHIELD), R8.2, R9.2; also elsewhere on the board

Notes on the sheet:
USB-C SERVICE INGRESS
USB 2.0 service connector, CC terminations and 5VSB isolation diode.
